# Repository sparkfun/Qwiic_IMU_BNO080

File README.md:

SparkFun Qwiic VR IMU with the BNO080
========================================

[*SparkX IMU BNO080 (BOB-14686)*](https://www.sparkfun.com/products/14686)

The BNO080/BNO085 IMU has a combination triple axis accelerometer/gyro/magnetometer packaged with an ARM Cortex M0+ running powerful algorithms. This enables the BNO080 Inertial Measurement Unit (IMU) to produce accurate rotation vector headings with an error of 5 degrees or less. It's what we've been waiting for: all the sensor data is combined into meaningful, accurate IMU information.

This IC was designed to be implemented in Android based cellular phones to handle all the computations necessary for virtual reality goggles using only your phone. The sensor is quite powerful but with power comes a complex interface. We've written an I<sup>2</sup>C based library that provides the rotation vector (the reading most folks want from an IMU) as well as raw acceleration, gyro, and magnetometer readings. The sensor is capable of communicating over SPI and UART as well!

In addition the BNO080 IMU provides a built-in step counter, tap detector, activity classifier (are you running, walking, or sitting still?), and a shake detector. We are duly impressed.

Repository Contents
-------------------

* **/Documents** - Datasheets
* **/Firmware** - Just the test routine for the testjig. Please see the [BNO080/BNO085 library](https://github.com/sparkfun/SparkFun_BNO080_Arduino_Library) for a large number of examples.
* **/Hardware** - Eagle design files (.brd, .sch)
* **/Software** - Processing Example showing how to manipulate graphics using quaternions

Library
--------------
* **[Arduino Library](https://github.com/sparkfun/SparkFun_BNO080_Arduino_Library)** - Library for reading Quaternions, raw accel/gyro/mag, reading activity classifier, advanced configuration, etc.

License Information
-------------------

This product is _**open source**_! 

Please review the LICENSE.md file for license information. 

If you have any questions or concerns on licensing, please contact techsupport@sparkfun.com.

Please use, reuse, and modify these files as you see fit. Please maintain attribution to SparkFun Electronics and release anyThing Development Board derivative under the same license.

Distributed as-is; no warranty is given.

- Your friends at SparkFun.

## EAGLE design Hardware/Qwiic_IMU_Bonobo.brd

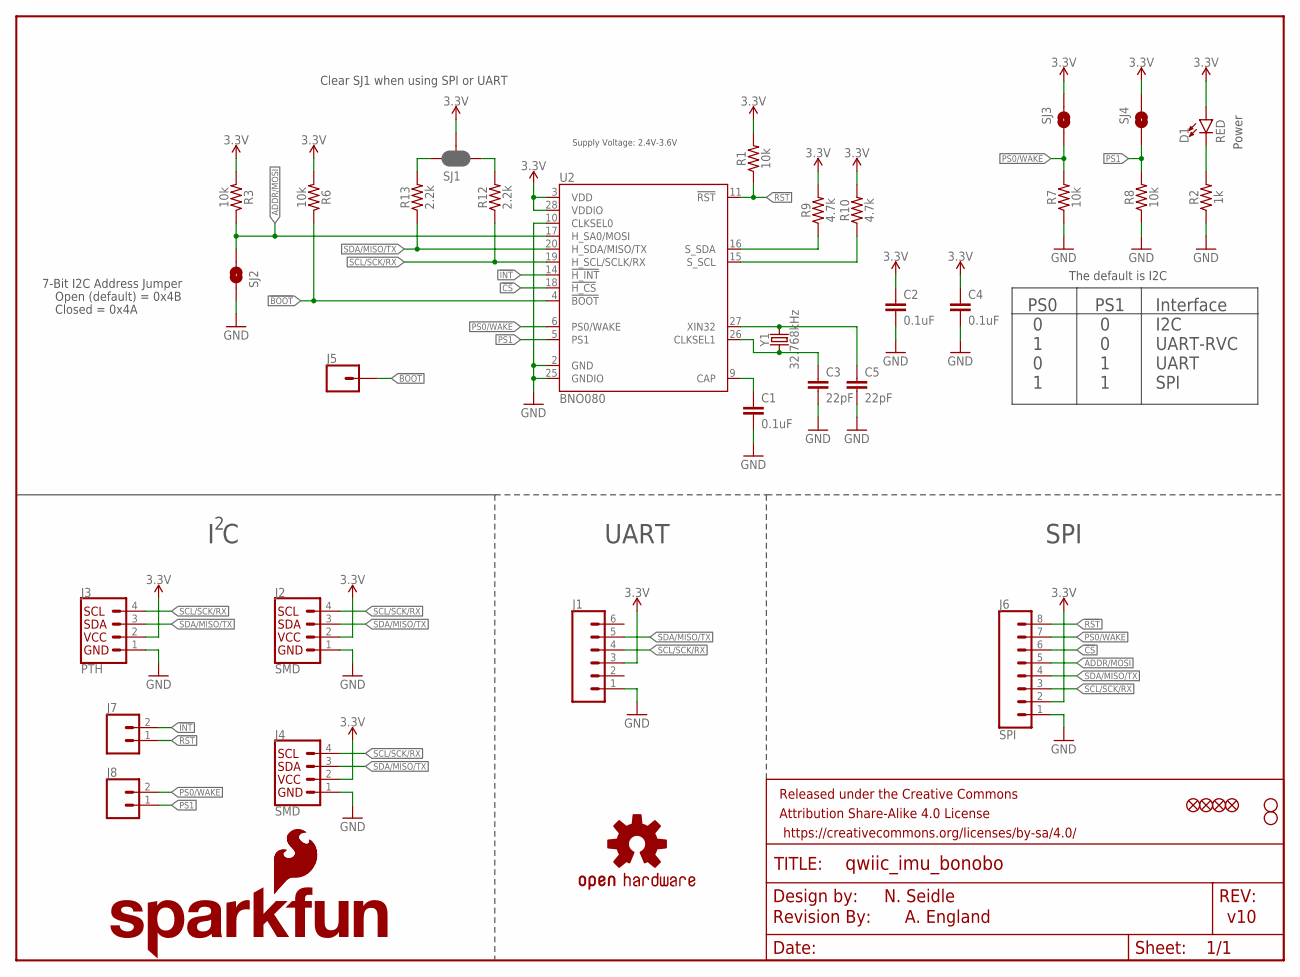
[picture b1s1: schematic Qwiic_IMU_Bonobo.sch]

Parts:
C1, C2, C4: 0.1uF; 0603
C3, C5: 22pF; 0603
D1: RED; LED-0603
FRAME1: FRAME-LETTER; CREATIVE_COMMONS
J1: CONN_06NO_SILK_FEMALE_PTH; 1X06_NO_SILK
J2, J4: SMD; 1X04_1MM_RA
J3: PTH; 1X04_NO_SILK
J5: CONN_01PTH_NO_SILK_YES_STOP; 1X01_NO_SILK
J6: SPI; 1X08_NO_SILK
J7, J8: CONN_021X02_NO_SILK; 1X02_NO_SILK
JP1, JP2, JP5, JP6: FIDUCIALUFIDUCIAL; MICRO-FIDUCIAL
JP3, JP4: STAND-OFF
LOGO1: OSHW-LOGOMINI; OSHW-LOGO-MINI
LOGO2: REVISION
LOGO4: SFE_LOGO_FLAME.1_INCH; SFE_LOGO_FLAME_.1
LOGO5: SFE_LOGO_NAME_FLAME.1_INCH; SFE_LOGO_NAME_FLAME_.1
R1, R3, R6, R7, R8: 10k; 0603
R2: 1k; 0603
R9, R10: 4.7k; 0603
R12, R13: 2.2k; 0603
SJ1: JUMPER-SMT_3_2-NC_PASTE_SILK; SMT-JUMPER_3_2-NC_PASTE_SILK
SJ2, SJ3, SJ4: SOLDERJUMPERNO; SJ_2S-NO
U2: BNO080; LGA-28
Y1: 32.768kHz; CRYSTAL-SMD-3.2X1.5MM

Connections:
3.3V: C2.1, C4.1, D1.A, J1.3, J2.2 (VCC), J3.2 (VCC), J4.2 (VCC), J6.2, R1.2, R3.2, R6.2, R9.2, R10.2, SJ1.2, SJ3.1, SJ4.1, U2.3 (VDD), U2.28 (VDDIO)
!BOOT: J5.1, R6.1, U2.4 (!BOOT)
!CS: J6.6, U2.18 (!H_CS)
!INT: J7.2, U2.14 (!H_INT)
!RST: J6.8, J7.1, R1.1, U2.11 (!RST)
ADDR/MOSI: J6.5, R3.1, SJ2.2, U2.17 (H_SA0/MOSI)
CAP: C1.1, U2.9 (CAP)
GND: C1.2, C2.2, C3.2, C4.2, C5.2, J1.1, J2.1 (GND), J3.1 (GND), J4.1 (GND), J6.1, R2.1, R7.1, R8.1, SJ2.1, U2.2 (GND), U2.10 (CLKSEL0), U2.25 (GNDIO)
unnamed: C5.1, U2.27 (XIN32), Y1.P$2 (2)
unnamed: C3.1, U2.26 (CLKSEL1), Y1.P$1 (1)
unnamed: D1.C, R2.2
PS0/WAKE: J6.7, J8.2, R7.2, SJ3.2, U2.6 (PS0/WAKE)
PS1: J8.1, R8.2, SJ4.2, U2.5 (PS1)
SCL/SCK/RX: J1.4, J2.4 (SCL), J3.4 (SCL), J4.4 (SCL), J6.3, R12.1, U2.19 (H_SCL/SCLK/RX)
SCL_PU: R12.2, SJ1.1
SDA/MISO/TX: J1.5, J2.3 (SDA), J3.3 (SDA), J4.3 (SDA), J6.4, R13.1, U2.20 (H_SDA/MISO/TX)
SDA_PU: R13.2, SJ1.3
S_SCL: R10.1, U2.15 (S_SCL)
S_SDA: R9.1, U2.16 (S_SDA)

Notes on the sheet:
N. Seidle
v10
7-Bit I2C Address Jumper
Closed = 0x4A
Open (default) = 0x4B
PS0 0 1 0 1
PS1 0 0 1 1
Interface I2C UART-RVC UART SPI
The default is I2C
Clear SJ1 when using SPI or UART
I C
UART
SPI
Power
A. England
Supply Voltage: 2.4V-3.6V

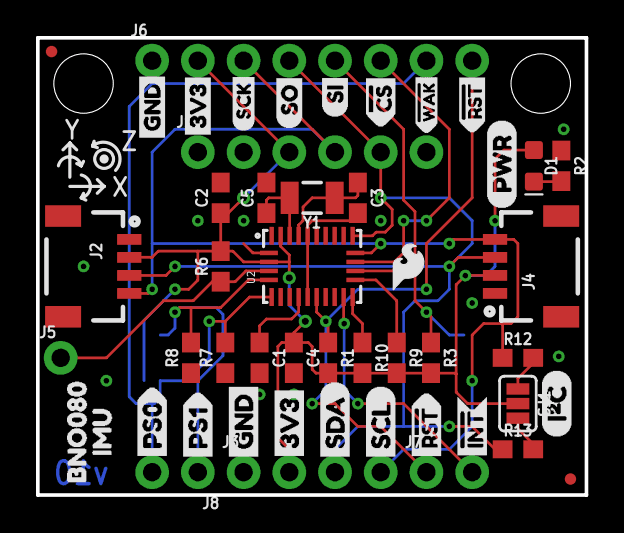
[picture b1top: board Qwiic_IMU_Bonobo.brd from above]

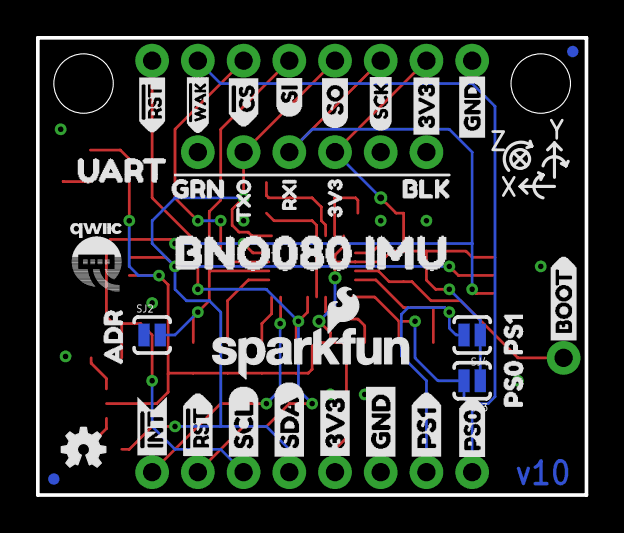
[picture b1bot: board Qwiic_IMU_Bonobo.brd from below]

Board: 2 copper layers, 30.5 x 25.4 mm, 89 parts (35 on the bottom side), 19 nets.

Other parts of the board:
U$1: (PWR)
U$2: BOOT2
U$3, U$4: #RST>
U$5, U$6: SCL
U$7, U$8: SDA
U$9, U$10: 3V3
U$11, U$50: 3V30
U$12, U$13: SCK0
U$14: PS03
U$15, U$16: GND
U$17, U$18: SI1
U$19, U$20: #WAK6
U$21: 3V32
U$22: RXI1
U$23: (I_SUPER2_C)
U$25, U$26: #INT0
U$27, U$28: PS14
U$29: PS05
U$30: ADR0
U$33: PS114
U$34: PS015
U$35: TXO0
U$39: UART8
U$40: GRN10
U$41: BLK9
U$42, U$43: GND1
U$44: BNO080_IMU11
U$46: BNO08012
U$47: IMU13
U$49, U$51: #RST7
U$52, U$53: #CS3
U$54, U$55: SO0
U$59: QWIIC#LABEL#FULL#M#PNG

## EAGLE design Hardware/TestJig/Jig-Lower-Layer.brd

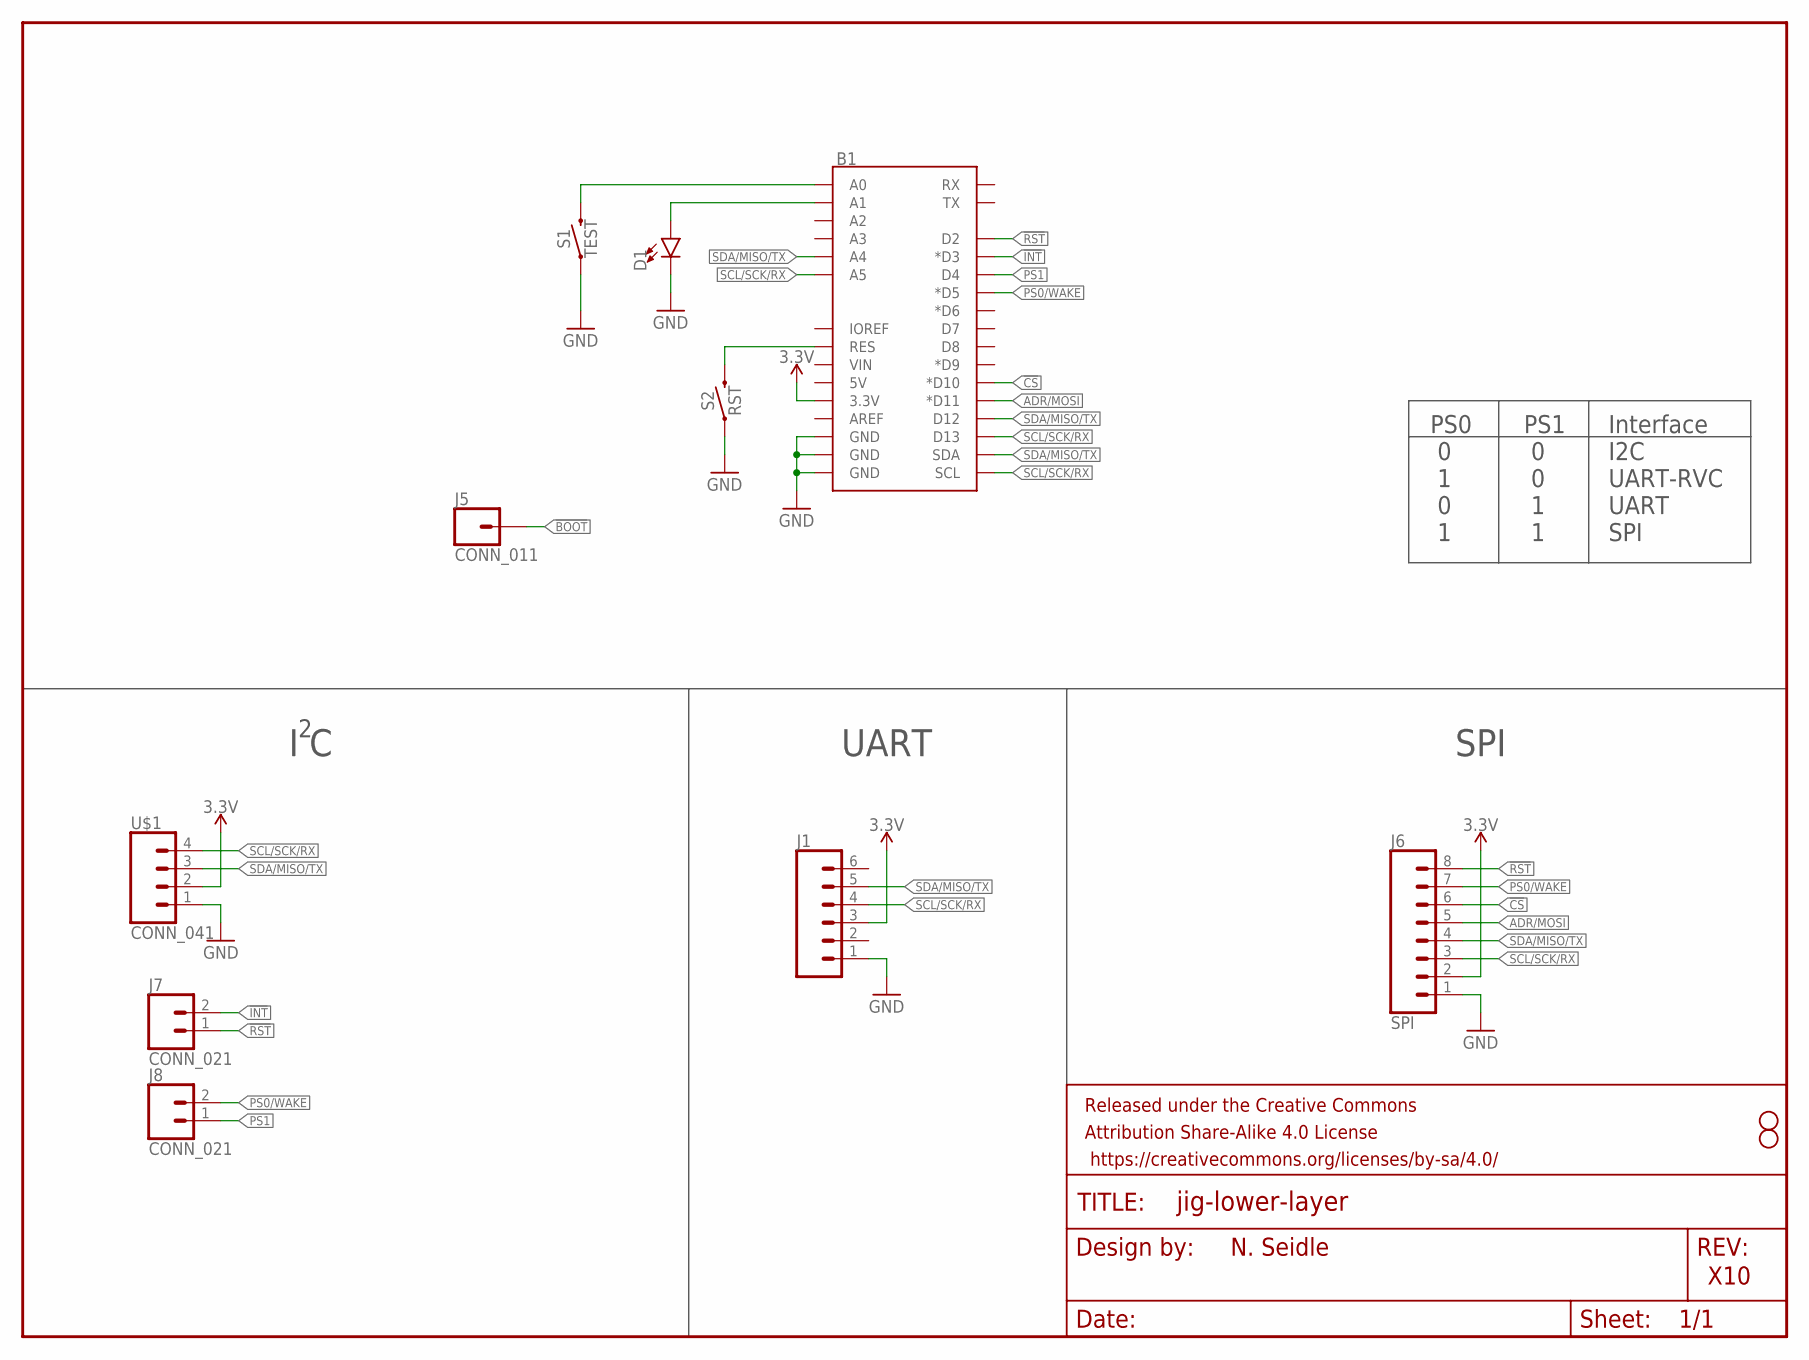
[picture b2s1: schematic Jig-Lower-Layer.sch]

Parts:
B1: ARDUINO_UNO_R3_SHIELDBASIC; UNO_R3_SHIELD
D1: LED5MM; LED_5MM
FRAME1: FRAME-LETTER; CREATIVE_COMMONS
J1: CONN_061; 1X06
J5: CONN_011; 1X01
J6: SPI; 1X08
J7, J8: CONN_021; 1X02
JP3, JP4: STAND-OFF
S1: TEST; TACTILE_SWITCH_PTH_12MM
S2: RST; TACTILE_SWITCH_PTH_12MM
U$1: CONN_041; 1X04

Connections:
3.3V: B1.3.3V, J1.3, J6.2, U$1.2
!BOOT: J5.1
!CS: B1.D10 (*D10), J6.6
!INT: B1.D3 (*D3), J7.2
!RST: B1.D2, J6.8, J7.1
ADR/MOSI: B1.D11 (*D11), J6.5
GND: B1.GND@0 (GND), B1.GND@1 (GND), B1.GND@2 (GND), D1.K (C), J1.1, J6.1, S1.1, S2.1, U$1.1
unnamed: B1.A0, S1.3 (2)
unnamed: B1.A1, D1.A
unnamed: B1.RES, S2.3 (2)
PS0/WAKE: B1.D5 (*D5), J6.7, J8.2
PS1: B1.D4, J8.1
SCL/SCK/RX: B1.A5, B1.D13, B1.SCL, J1.4, J6.3, U$1.4
SDA/MISO/TX: B1.A4, B1.D12, B1.SDA, J1.5, J6.4, U$1.3

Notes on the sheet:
N. Seidle
X10
PS0 0 1 0 1
PS1 0 0 1 1
Interface I2C UART-RVC UART SPI
I C
UART
SPI

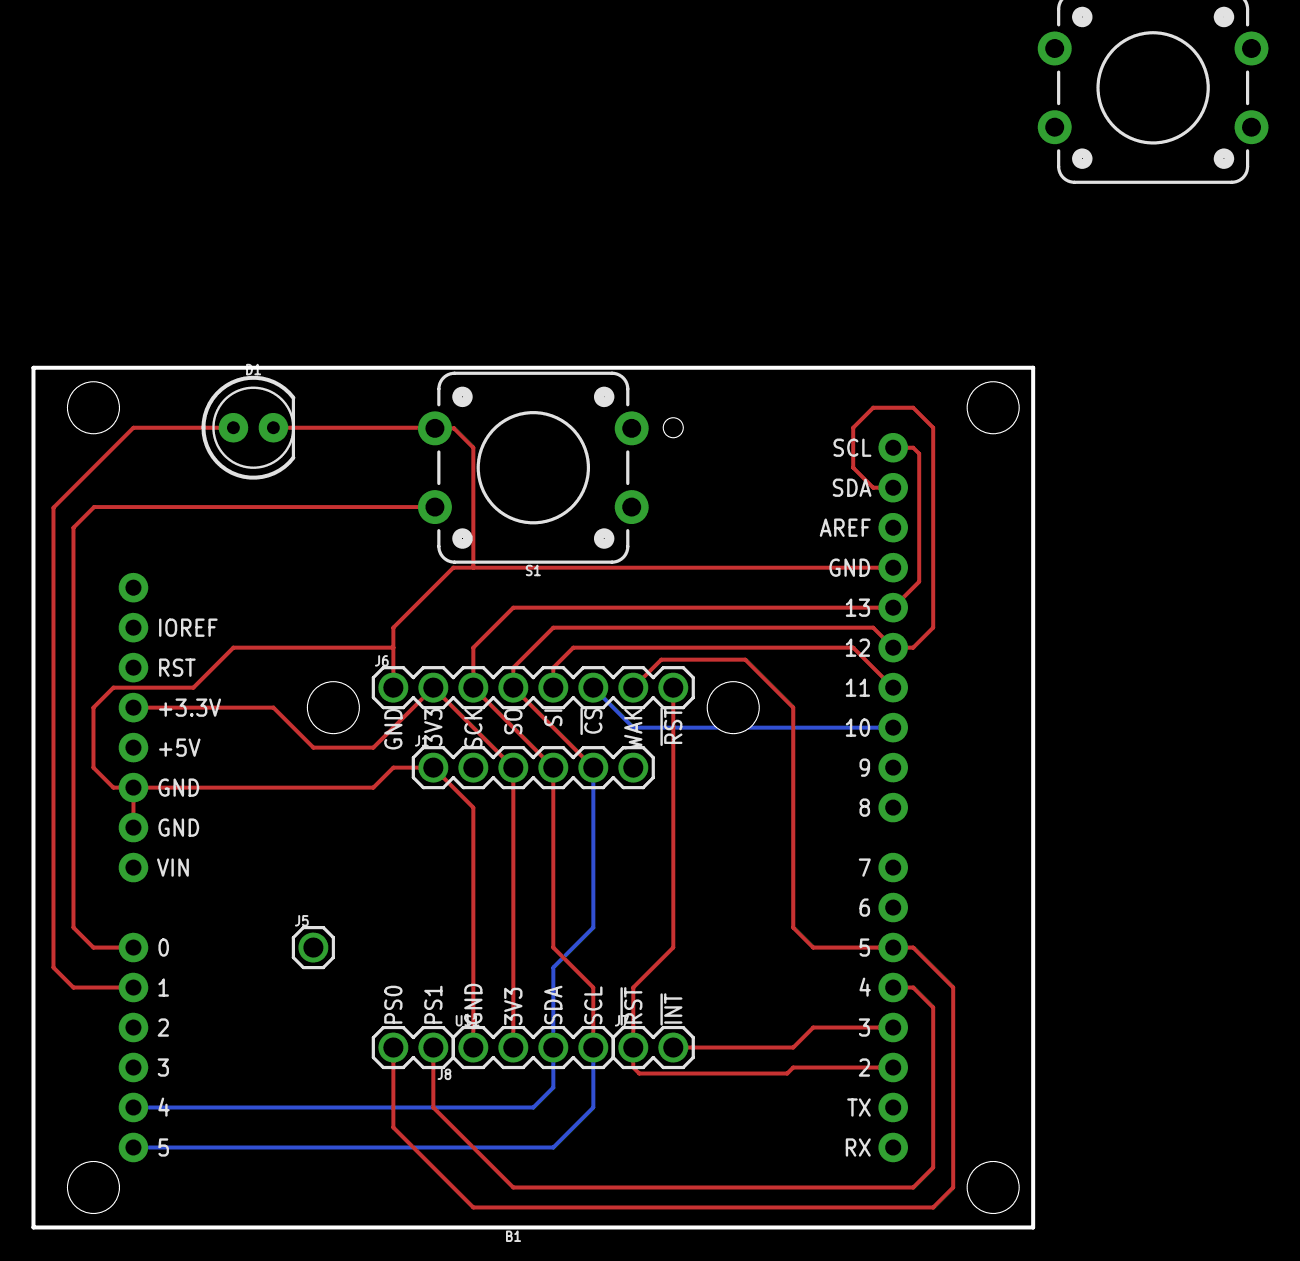
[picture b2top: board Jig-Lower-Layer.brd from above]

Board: 2 copper layers, 63.5 x 54.6 mm, 17 parts (0 on the bottom side), 13 nets.

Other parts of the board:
JP1, JP2, JP5, JP6: STAND-OFF

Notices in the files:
parts and their libraries:
SparkFun-Resistors: Licensing: Creative Commons ShareAlike 4.0 International - https://creativecommons.org/licenses/by-sa/4.0
SparkFun-Aesthetics: Released under the Creative Commons Attribution Share-Alike 4.0 License
SparkFun-Aesthetics: https://creativecommons.org/licenses/by-sa/4.0
